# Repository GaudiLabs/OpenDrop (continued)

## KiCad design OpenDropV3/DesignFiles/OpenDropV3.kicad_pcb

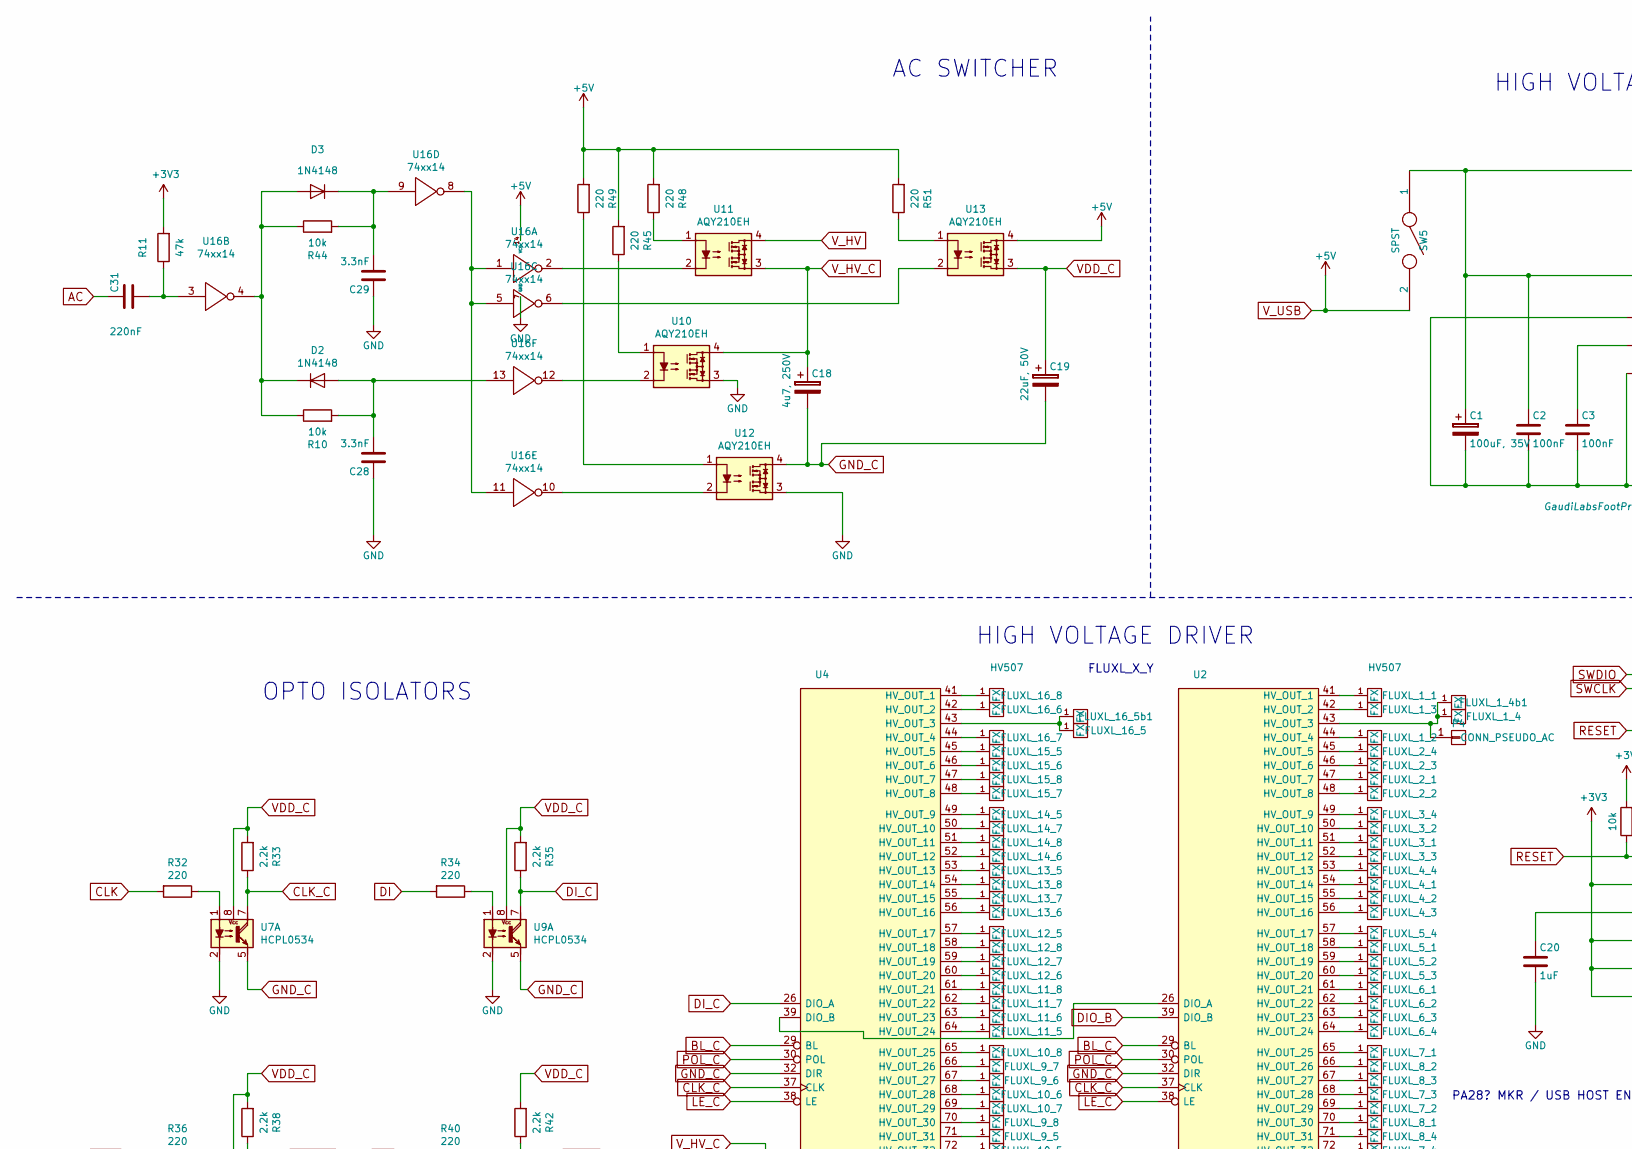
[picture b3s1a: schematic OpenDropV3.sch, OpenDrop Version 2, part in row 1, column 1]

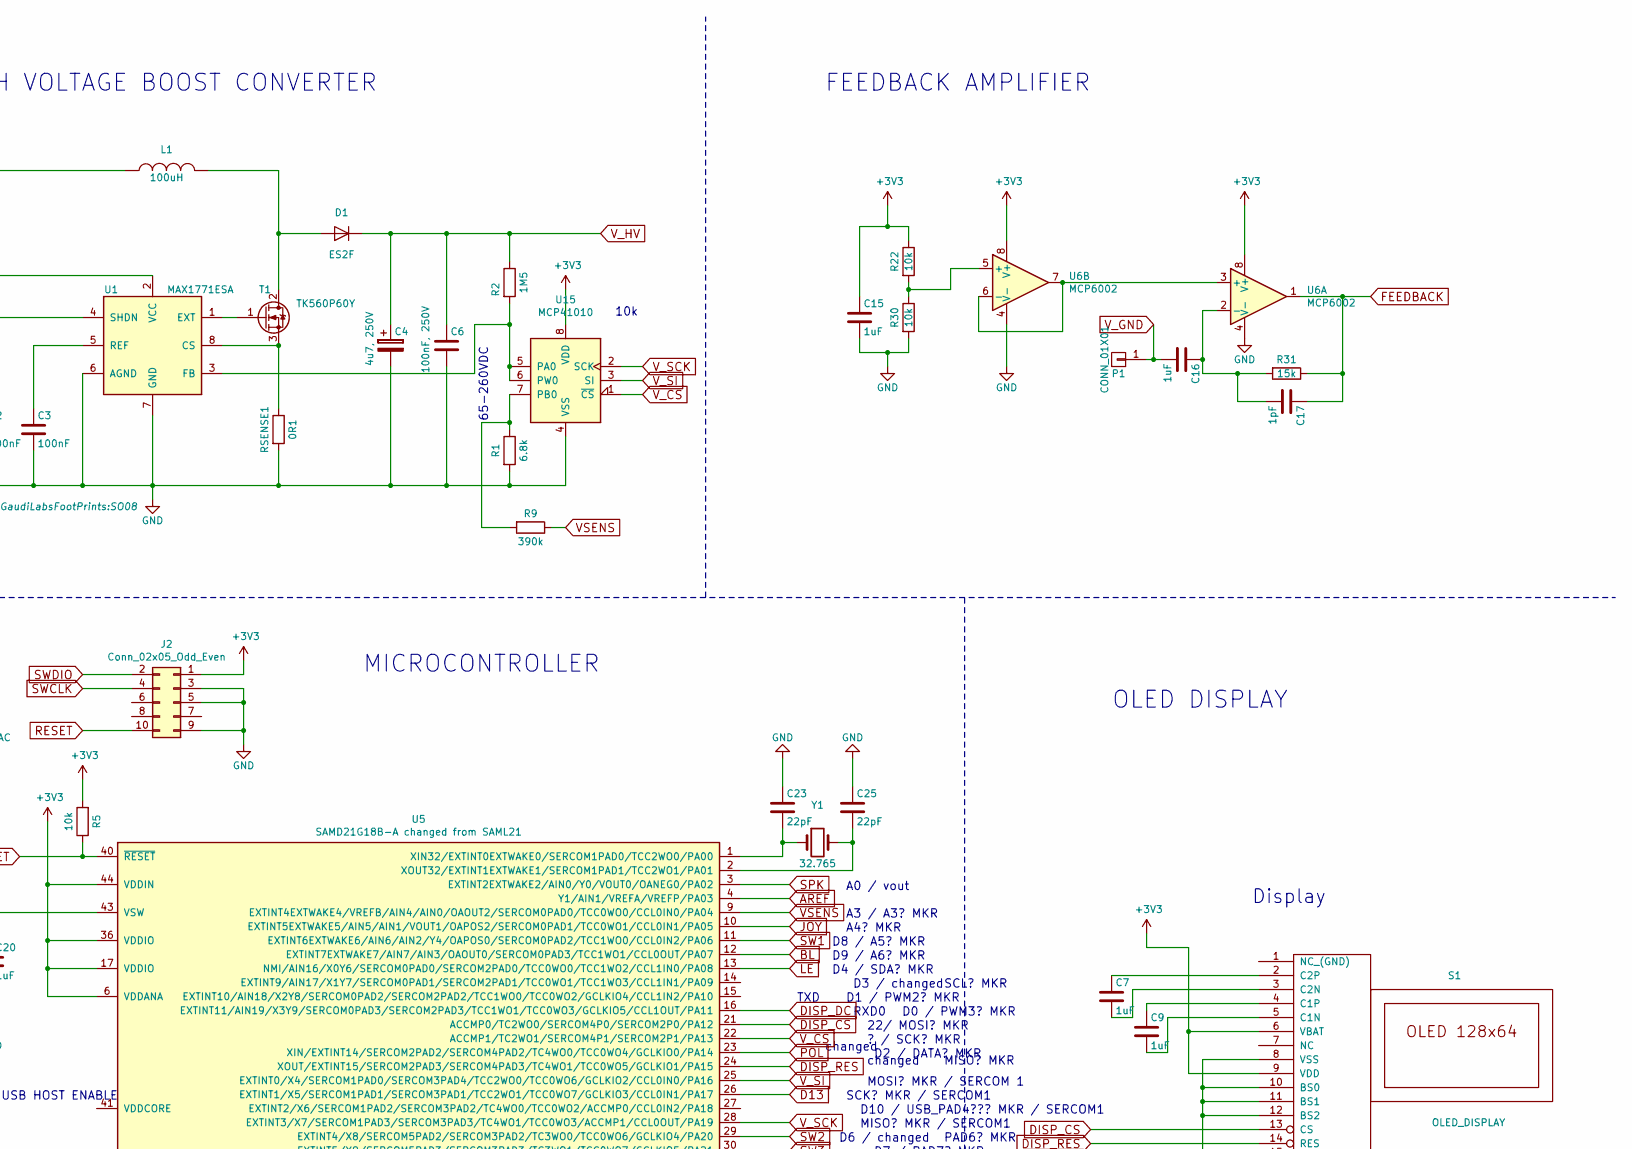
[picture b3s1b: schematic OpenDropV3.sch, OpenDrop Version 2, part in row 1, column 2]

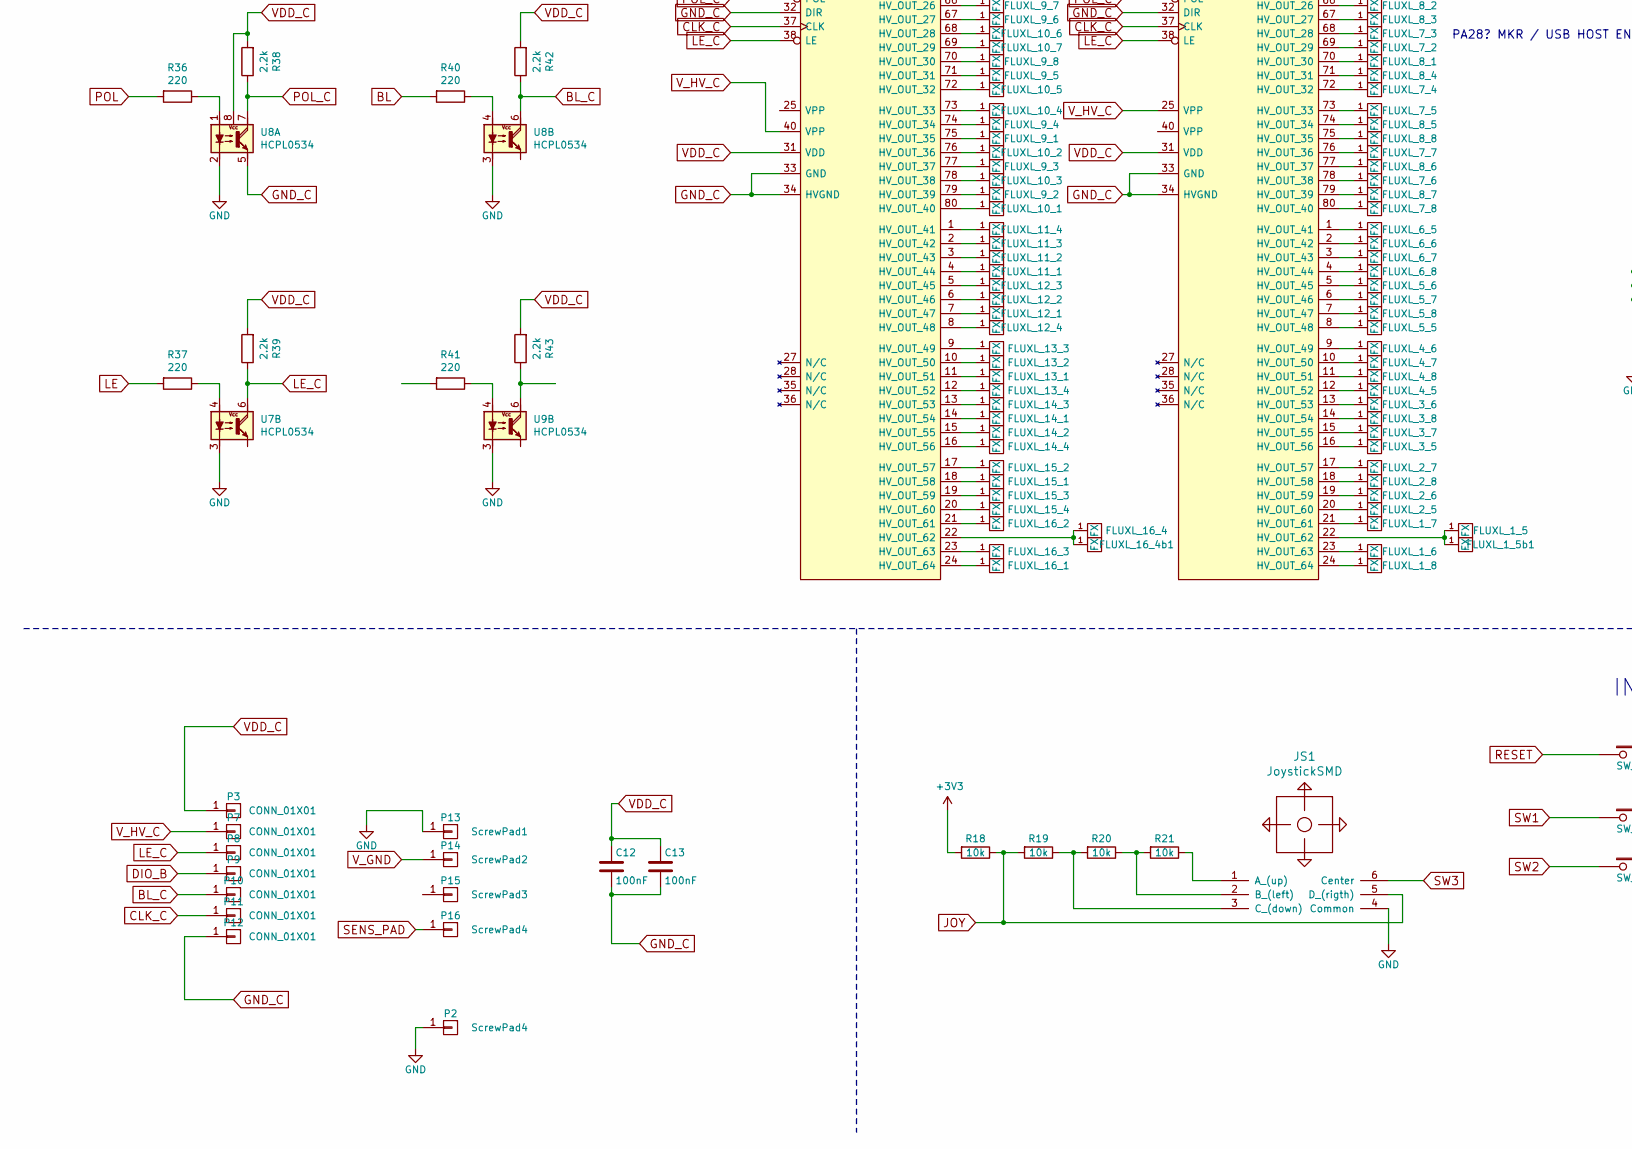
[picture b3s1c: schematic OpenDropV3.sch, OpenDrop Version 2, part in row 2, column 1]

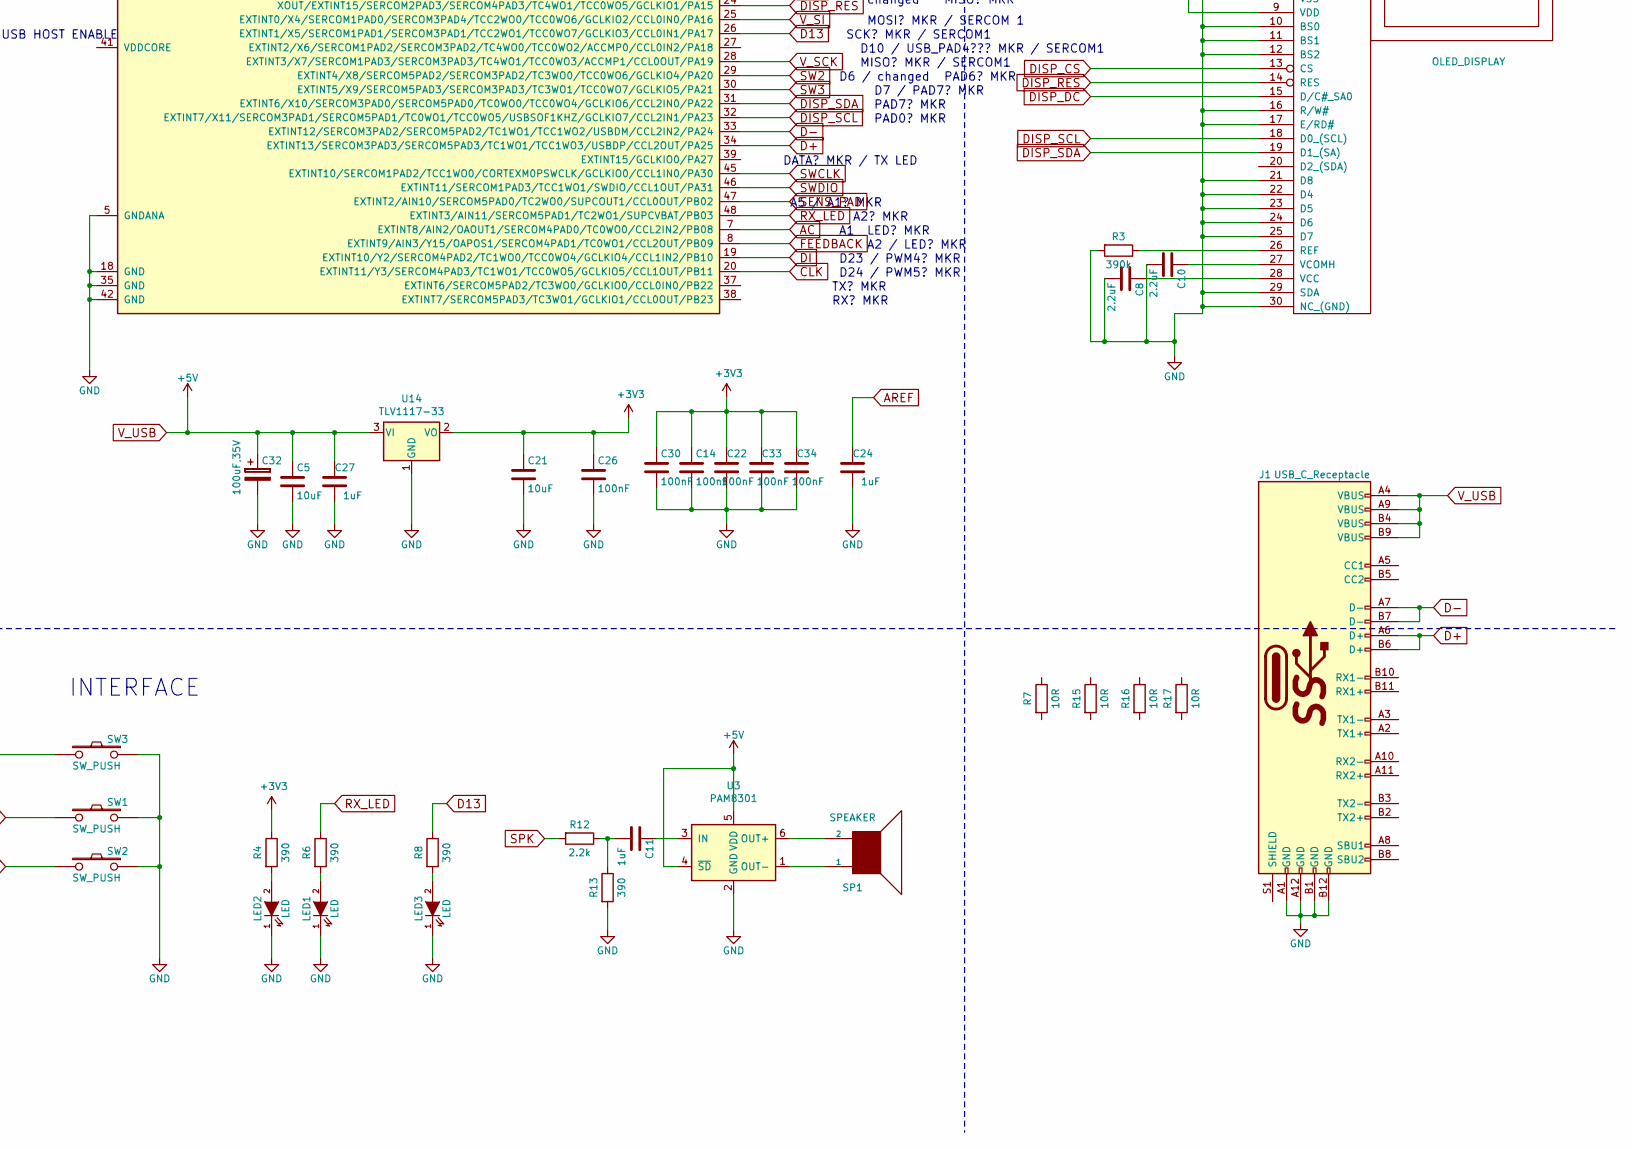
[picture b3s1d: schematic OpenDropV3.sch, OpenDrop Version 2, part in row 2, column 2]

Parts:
C1: 100uF, 35V; R_2512_HandSoldering
C2, C3, C12, C13, C14, C22, C26, C30, C33, C34: 100nF; C_0805
C4, C18: 4u7, 250V; c_elec_10x10
C5, C21: 10uF; C_1206
C6: 100nF, 250V; C_1913
C7, C9, C11, C15, C16, C20, C24, C27: 1uF; C_0805
C8, C10: 2.2uF; C_0805
C17: 1pF; C_0805
C19: 22uF, 50V; c_elec_6.3x5.8
C23, C25: 22pF; C_0805
C28, C29: 3.3nF; C_0805
C31: 220nF; C_0805
C32: 100uF,35V; R_2512_HandSoldering
D1: ES2F; DO-214AA
D2, D3: 1N4148; D_SOD-323
FLUXL_1_1, FLUXL_1_8, FLUXL_16_1, FLUXL_16_8: FX; FLUXPAD_2_75_4MIL_4_5_res3
FLUXL_1_2, FLUXL_1_7, FLUXL_16_2, FLUXL_16_7: FX; FLUXPAD_2_75_4MIL_4_5_res1
FLUXL_1_3, FLUXL_1_6, FLUXL_16_3, FLUXL_16_6: FX; FLUXPAD_2_75_4MIL_4_5_res2
FLUXL_1_4, FLUXL_1_5, FLUXL_16_4, FLUXL_16_5: FX; FLUXPAD_2_75_4MIL_4_5_res4
FLUXL_1_4b1, FLUXL_1_5b1, FLUXL_16_4b1, FLUXL_16_5b1: FX; FLUXPAD_2_75_4MIL_4_5_res5
FLUXL_2_1, FLUXL_15_8: FX; FLUXPAD_2_75_4MIL_4_5_topleft
FLUXL_2_2, FLUXL_2_7, FLUXL_3_2, FLUXL_3_3, FLUXL_3_4, FLUXL_3_5, FLUXL_3_6, FLUXL_3_7, FLUXL_4_2, FLUXL_4_3, FLUXL_4_4, FLUXL_4_5, FLUXL_4_6, FLUXL_4_7, FLUXL_5_2, FLUXL_5_3, FLUXL_5_4, FLUXL_5_5, FLUXL_5_6, FLUXL_5_7, FLUXL_6_2, FLUXL_6_3, FLUXL_6_4, FLUXL_6_5, FLUXL_6_6, FLUXL_6_7, FLUXL_7_2, FLUXL_7_3, FLUXL_7_4, FLUXL_7_5, FLUXL_7_6, FLUXL_7_7, FLUXL_8_2, FLUXL_8_3, FLUXL_8_4, FLUXL_8_5, FLUXL_8_6, FLUXL_8_7, FLUXL_9_2, FLUXL_9_3, FLUXL_9_4, FLUXL_9_5, FLUXL_9_6, FLUXL_9_7, FLUXL_10_2, FLUXL_10_3, FLUXL_10_4, FLUXL_10_5, FLUXL_10_6, FLUXL_10_7, FLUXL_11_2, FLUXL_11_3, FLUXL_11_4, FLUXL_11_5, FLUXL_11_6, FLUXL_11_7, FLUXL_12_2, FLUXL_12_3, FLUXL_12_4, FLUXL_12_5, FLUXL_12_6, FLUXL_12_7, FLUXL_13_2, FLUXL_13_3, FLUXL_13_4, FLUXL_13_5, FLUXL_13_6, FLUXL_13_7, FLUXL_14_2, FLUXL_14_3, FLUXL_14_4, FLUXL_14_5, FLUXL_14_6, FLUXL_14_7, FLUXL_15_2, FLUXL_15_7: FX; FLUXPAD_2_75_4MIL_4_5
FLUXL_2_3, FLUXL_2_4, FLUXL_2_5, FLUXL_2_6, FLUXL_15_3, FLUXL_15_4, FLUXL_15_5, FLUXL_15_6: FX; FLUXPAD_2_75_4MIL_4_5_side
FLUXL_2_8, FLUXL_15_1: FX; FLUXPAD_2_75_4MIL_4_5_topright
FLUXL_3_1, FLUXL_3_8, FLUXL_4_1, FLUXL_4_8, FLUXL_5_1, FLUXL_5_8, FLUXL_6_1, FLUXL_6_8, FLUXL_7_1, FLUXL_7_8, FLUXL_8_1, FLUXL_8_8, FLUXL_9_1, FLUXL_9_8, FLUXL_10_1, FLUXL_10_8, FLUXL_11_1, FLUXL_11_8, FLUXL_12_1, FLUXL_12_8, FLUXL_13_1, FLUXL_13_8, FLUXL_14_1, FLUXL_14_8: FX; FLUXPAD_2_75_4MIL_4_5_top
J1: USB_C_Receptacle; USB_C_Receptacle_Amphenol_12401610E4-2A
J2: Conn_02x05_Odd_Even; Pin_Header_Straight_2x05_Pitch1.27mm_SMD
JS1: JoystickSMD; JoystickSMD_SKQUSeries
L1: 100uH; SRN1060
LED1, LED2, LED3: LED; LED-0805
P1, P3, P7, P8, P9, P10, P11, P12: CONN_01X01; Measurement_Point_Square-SMD-Pad_Small
P2: ScrewPad4; Measurement_Point_Croki
P4: CONN_PSEUDO_AC; Measurement_Point_Square-SMD-Pad_Small
P13: ScrewPad1; MountingHolePad_3x9mm
P14: ScrewPad2; MountingHolePad_3x9mm
P15: ScrewPad3; MountingHolePad_3x9mm
P16: ScrewPad4; MountingHolePad_3x9mm
R1: 6.8k; R_0805
R2: 1M5; R_2512
R3, R9: 390k; R_0805
R4, R6, R8, R13: 390; R_0805
R5, R10, R18, R19, R20, R21, R22, R30, R44: 10k; R_0805
R7, R15, R16, R17: 10R; R_0805_HeatPad
R11: 47k; R_0805
R12, R33, R35, R38, R39, R42, R43: 2.2k; R_0805
R31: 15k; R_0805
R32, R34, R36, R37, R40, R41, R45, R48, R49, R51: 220; R_0805
RSENSE1: 0R1; R_2010
S1: OLED_DISPLAY; OLED_096_1_Flip
SP1: SPEAKER; Speaker16mm
SW1, SW2: SW_PUSH; PUSH_BUTTON_SMD
SW3: SW_PUSH; SW_SPST_KMS221GLFS
SW5: SPST; Switch_On-On
T1: TK560P60Y; D-Pak_TO252AA
U1: MAX1771ESA; SO08
U2, U4: HV507; PQFP-80_14x20mm_Pitch0.8mm
U3: PAM8301; SOT-23-6
U5: SAMD21G18B-A changed from SAML21; TQFP-48_7x7mm_Pitch0.5mm
U6: MCP6002; SO08
U7, U8, U9: HCPL0534; HCPL_Optocoupler_SMD
U10, U11, U12, U13: AQY210EH; SMD_DIP4
U14: TLV1117-33; SOT-223
U15: MCP41010; SO08
U16: 74xx14; SOIC-14_N
Y1: 32.765; Crystal_SMD_3215-2pin_3.2x1.5mm

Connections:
+3V3: C14.1, C15.1, C21.1, C22.2, C26.1, C30.1, C33.2, C34.2, J2.1, R4.1, R5.2, R11.2, R18.2, R22.1, S1.6 (VBAT), S1.9 (VDD), U5.6 (VDDANA), U5.17 (VDDIO), U5.36 (VDDIO), U5.44 (VDDIN), U6.8 (V+), U14.2 (VO), U15.8 (VDD)
AC: C31.1, U5.7 (EXTINT8/AIN2/OAOUT1/SERCOM4PAD0/TC0WO0/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)
AREF: C24.2, U5.4 (Y1/AIN1/VREFA/VREFP/PA03)
BL: R40.2, U5.12 (EXTINT7EXTWAKE7/AIN7/AIN3/OAOUT0/SERCOM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)
BL_C: P10.1, R42.1, U2.29 (BL), U4.29 (BL), U8.6 (COLLECTOR)
CLK: R32.2, U5.20 (EXTINT11/Y3/SERCOM4PAD3/TC1WO1/TCC0WO5/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)
CLK_C: P11.1, R33.1, U2.37 (CLK), U4.37 (CLK), U7.7 (COLLECTOR)
D13: R8.1, U5.26 (EXTINT1/X5/SERCOM1PAD1/SERCOM3PAD1/TCC2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)
D+: J1.A6 (D+), J1.B6 (D+), U5.34 (EXTINT13/SERCOM3PAD3/SERCOM5PAD3/TC1WO1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)
D-: J1.A7 (D-), J1.B7 (D-), U5.33 (EXTINT12/SERCOM3PAD2/SERCOM5PAD2/TC1WO1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)
DI: R34.2, U5.19 (EXTINT10/Y2/SERCOM4PAD2/TC1WO0/TCC0WO4/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)
DIO_B: P9.1, U2.39 (DIO_B)
DISP_CS: S1.13 (CS), U5.21 (ACCMP0/TC2WO0/SERCOM4P0/SERCOM2P0/PA12)
DISP_DC: S1.15 (D/C#_SA0), U5.16 (EXTINT11/AIN19/X3Y9/SERCOM0PAD3/SERCOM2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)
DISP_RES: S1.14 (RES), U5.24 (XOUT/EXTINT15/SERCOM2PAD3/SERCOM4PAD3/T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)
DISP_SCL: S1.18 (D0_(SCL)), U5.32 (EXTINT7/X11/SERCOM3PAD1/SERCOM5PAD1/TC0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)
DISP_SDA: S1.19 (D1_(SA)), U5.31 (EXTINT6/X10/SERCOM3PAD0/SERCOM5PAD0/TC0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)
DI_C: R35.1, U4.26 (DIO_A), U9.7 (COLLECTOR)
FEEDBACK: C17.1, R31.1, U5.8 (EXTINT9/AIN3/Y15/OAPOS1/SERCOM4PAD1/TC0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), U6.1
GND: C1.2, C2.2, C3.2, C4.2, C5.2, C6.2, C8.2, C10.2, C14.2, C15.2, C20.2, C21.2, C22.1, C23.1, C24.1, C25.1, C26.2, C27.1, C28.1, C29.1, C30.2, C32.2, C33.1, C34.1, J1.A1 (GND), J1.A12 (GND), J1.B1 (GND), J1.B12 (GND), J2.3, J2.5, J2.9, JS1.4 (Common), LED1.1 (K), LED2.1 (K), LED3.1 (K), P2.1, P13.1, R1.2, R3.2, R13.2, R30.2, RSENSE1.2, S1.8 (VSS), S1.10 (BS0), S1.11 (BS1), S1.12 (BS2), S1.16 (R/W#), S1.17 (E/RD#), S1.21 (D8), S1.22 (D4), S1.23 (D5), S1.24 (D6), S1.25 (D7), S1.29 (SDA), S1.30 (NC_(GND)), SW1.2, SW2.2, SW3.2, U1.4 (SHDN), U1.6 (AGND), U1.7 (GND), U3.2 (GND), U5.5 (GNDANA), U5.18 (GND), U5.35 (GND), U5.42 (GND), U6.4 (V-), U7.2 (CATHODE), U7.3 (CATHODE), U8.2 (CATHODE), U8.3 (CATHODE), U9.2 (CATHODE), U9.3 (CATHODE), U10.3, U12.3, U14.1 (GND), U15.4 (VSS), U16.7 (GND)
GND_C: C12.2, C13.2, C18.2, C19.2, P12.1, U2.32 (DIR), U2.33 (GND), U2.34 (HVGND), U4.32 (DIR), U4.33 (GND), U4.34 (HVGND), U7.5, U8.5, U9.5, U12.4
JOY: JS1.5 (D_(rigth)), R18.1, R19.2, U5.10 (EXTINT5EXTWAKE5/AIN5/AIN1/VOUT1/OAPOS2/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)
LE: R37.2, U5.13 (NMI/AIN16/X0Y6/SERCOM0PAD0/SERCOM2PAD0/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)
LE_C: P8.1, R39.1, U2.38 (LE), U4.38 (LE), U7.6 (COLLECTOR)
unnamed: C1.1, C2.1, L1.1, SW5.1, U1.2 (VCC)
unnamed: C3.1, U1.5 (REF)
unnamed: C7.1, S1.2 (C2P)
unnamed: C7.2, S1.3 (C2N)
unnamed: C8.1, S1.28 (VCC)
unnamed: C9.1, S1.4 (C1P)
unnamed: C9.2, S1.5 (C1N)
unnamed: C10.1, S1.27 (VCOMH)
unnamed: C11.1, R12.1, R13.1
unnamed: C11.2, U3.3 (IN)
unnamed: C16.1, C17.2, R31.2, U6.2 (-)
unnamed: C20.1, U5.43 (VSW)
unnamed: C23.2, U5.1 (XIN32/EXTINT0EXTWAKE0/SERCOM1PAD0/TCC2W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), Y1.1
unnamed: C25.2, U5.2 (XOUT32/EXTINT1EXTWAKE1/SERCOM1PAD1/TCC2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), Y1.2
unnamed: C28.2, D2.2 (A), R10.2, U16.13
unnamed: C29.2, D3.1 (K), R44.2, U16.9
unnamed: C31.2, R11.1, U16.3
unnamed: D1.2 (A), L1.2, T1.2 (D)
unnamed: D2.1 (K), D3.2 (A), R10.1, R44.1, U16.4
unnamed: FLUXL_1_1.1, U2.41 (HV_OUT_1)
unnamed: FLUXL_1_2.1, U2.44 (HV_OUT_4)
unnamed: FLUXL_1_3.1, U2.42 (HV_OUT_2)
unnamed: FLUXL_1_4.1, FLUXL_1_4b1.1, P4.1, U2.43 (HV_OUT_3)
unnamed: FLUXL_1_5.1, FLUXL_1_5b1.1, U2.22 (HV_OUT_62)
unnamed: FLUXL_1_6.1, U2.23 (HV_OUT_63)
unnamed: FLUXL_1_7.1, U2.21 (HV_OUT_61)
unnamed: FLUXL_1_8.1, U2.24 (HV_OUT_64)
unnamed: FLUXL_2_1.1, U2.47 (HV_OUT_7)
unnamed: FLUXL_2_2.1, U2.48 (HV_OUT_8)
unnamed: FLUXL_2_3.1, U2.46 (HV_OUT_6)
unnamed: FLUXL_2_4.1, U2.45 (HV_OUT_5)
unnamed: FLUXL_2_5.1, U2.20 (HV_OUT_60)
unnamed: FLUXL_2_6.1, U2.19 (HV_OUT_59)
unnamed: FLUXL_2_7.1, U2.17 (HV_OUT_57)
unnamed: FLUXL_2_8.1, U2.18 (HV_OUT_58)
unnamed: FLUXL_3_1.1, U2.51 (HV_OUT_11)
unnamed: FLUXL_3_2.1, U2.50 (HV_OUT_10)
unnamed: FLUXL_3_3.1, U2.52 (HV_OUT_12)
unnamed: FLUXL_3_4.1, U2.49 (HV_OUT_9)
unnamed: FLUXL_3_5.1, U2.16 (HV_OUT_56)
unnamed: FLUXL_3_6.1, U2.13 (HV_OUT_53)
unnamed: FLUXL_3_7.1, U2.15 (HV_OUT_55)
unnamed: FLUXL_3_8.1, U2.14 (HV_OUT_54)
unnamed: FLUXL_4_1.1, U2.54 (HV_OUT_14)
unnamed: FLUXL_4_2.1, U2.55 (HV_OUT_15)
unnamed: FLUXL_4_3.1, U2.56 (HV_OUT_16)
unnamed: FLUXL_4_4.1, U2.53 (HV_OUT_13)
unnamed: FLUXL_4_5.1, U2.12 (HV_OUT_52)
unnamed: FLUXL_4_6.1, U2.9 (HV_OUT_49)
unnamed: FLUXL_4_7.1, U2.10 (HV_OUT_50)
unnamed: FLUXL_4_8.1, U2.11 (HV_OUT_51)
unnamed: FLUXL_5_1.1, U2.58 (HV_OUT_18)
unnamed: FLUXL_5_2.1, U2.59 (HV_OUT_19)
unnamed: FLUXL_5_3.1, U2.60 (HV_OUT_20)
unnamed: FLUXL_5_4.1, U2.57 (HV_OUT_17)
unnamed: FLUXL_5_5.1, U2.8 (HV_OUT_48)
unnamed: FLUXL_5_6.1, U2.5 (HV_OUT_45)
unnamed: FLUXL_5_7.1, U2.6 (HV_OUT_46)
unnamed: FLUXL_5_8.1, U2.7 (HV_OUT_47)
unnamed: FLUXL_6_1.1, U2.61 (HV_OUT_21)
unnamed: FLUXL_6_2.1, U2.62 (HV_OUT_22)
unnamed: FLUXL_6_3.1, U2.63 (HV_OUT_23)
unnamed: FLUXL_6_4.1, U2.64 (HV_OUT_24)
unnamed: FLUXL_6_5.1, U2.1 (HV_OUT_41)
unnamed: FLUXL_6_6.1, U2.2 (HV_OUT_42)
unnamed: FLUXL_6_7.1, U2.3 (HV_OUT_43)
unnamed: FLUXL_6_8.1, U2.4 (HV_OUT_44)
unnamed: FLUXL_7_1.1, U2.65 (HV_OUT_25)
unnamed: FLUXL_7_2.1, U2.69 (HV_OUT_29)
unnamed: FLUXL_7_3.1, U2.68 (HV_OUT_28)
unnamed: FLUXL_7_4.1, U2.72 (HV_OUT_32)
unnamed: FLUXL_7_5.1, U2.73 (HV_OUT_33)
unnamed: FLUXL_7_6.1, U2.78 (HV_OUT_38)
unnamed: FLUXL_7_7.1, U2.76 (HV_OUT_36)
unnamed: FLUXL_7_8.1, U2.80 (HV_OUT_40)
unnamed: FLUXL_8_1.1, U2.70 (HV_OUT_30)
unnamed: FLUXL_8_2.1, U2.66 (HV_OUT_26)
unnamed: FLUXL_8_3.1, U2.67 (HV_OUT_27)
unnamed: FLUXL_8_4.1, U2.71 (HV_OUT_31)
unnamed: FLUXL_8_5.1, U2.74 (HV_OUT_34)
unnamed: FLUXL_8_6.1, U2.77 (HV_OUT_37)
unnamed: FLUXL_8_7.1, U2.79 (HV_OUT_39)
unnamed: FLUXL_8_8.1, U2.75 (HV_OUT_35)
unnamed: FLUXL_9_1.1, U4.75 (HV_OUT_35)
unnamed: FLUXL_9_2.1, U4.79 (HV_OUT_39)
unnamed: FLUXL_9_3.1, U4.77 (HV_OUT_37)
unnamed: FLUXL_9_4.1, U4.74 (HV_OUT_34)
unnamed: FLUXL_9_5.1, U4.71 (HV_OUT_31)
unnamed: FLUXL_9_6.1, U4.67 (HV_OUT_27)
unnamed: FLUXL_9_7.1, U4.66 (HV_OUT_26)
unnamed: FLUXL_9_8.1, U4.70 (HV_OUT_30)
unnamed: FLUXL_10_1.1, U4.80 (HV_OUT_40)
unnamed: FLUXL_10_2.1, U4.76 (HV_OUT_36)
unnamed: FLUXL_10_3.1, U4.78 (HV_OUT_38)
unnamed: FLUXL_10_4.1, U4.73 (HV_OUT_33)
unnamed: FLUXL_10_5.1, U4.72 (HV_OUT_32)
unnamed: FLUXL_10_6.1, U4.68 (HV_OUT_28)
unnamed: FLUXL_10_7.1, U4.69 (HV_OUT_29)
unnamed: FLUXL_10_8.1, U4.65 (HV_OUT_25)
unnamed: FLUXL_11_1.1, U4.4 (HV_OUT_44)
unnamed: FLUXL_11_2.1, U4.3 (HV_OUT_43)
unnamed: FLUXL_11_3.1, U4.2 (HV_OUT_42)
unnamed: FLUXL_11_4.1, U4.1 (HV_OUT_41)
unnamed: FLUXL_11_5.1, U4.64 (HV_OUT_24)
unnamed: FLUXL_11_6.1, U4.63 (HV_OUT_23)
unnamed: FLUXL_11_7.1, U4.62 (HV_OUT_22)
unnamed: FLUXL_11_8.1, U4.61 (HV_OUT_21)
unnamed: FLUXL_12_1.1, U4.7 (HV_OUT_47)
unnamed: FLUXL_12_2.1, U4.6 (HV_OUT_46)
unnamed: FLUXL_12_3.1, U4.5 (HV_OUT_45)
unnamed: FLUXL_12_4.1, U4.8 (HV_OUT_48)
unnamed: FLUXL_12_5.1, U4.57 (HV_OUT_17)
unnamed: FLUXL_12_6.1, U4.60 (HV_OUT_20)
unnamed: FLUXL_12_7.1, U4.59 (HV_OUT_19)
unnamed: FLUXL_12_8.1, U4.58 (HV_OUT_18)
unnamed: FLUXL_13_1.1, U4.11 (HV_OUT_51)
unnamed: FLUXL_13_2.1, U4.10 (HV_OUT_50)
unnamed: FLUXL_13_3.1, U4.9 (HV_OUT_49)
unnamed: FLUXL_13_4.1, U4.12 (HV_OUT_52)
unnamed: FLUXL_13_5.1, U4.53 (HV_OUT_13)
unnamed: FLUXL_13_6.1, U4.56 (HV_OUT_16)
unnamed: FLUXL_13_7.1, U4.55 (HV_OUT_15)
unnamed: FLUXL_13_8.1, U4.54 (HV_OUT_14)
unnamed: FLUXL_14_1.1, U4.14 (HV_OUT_54)
unnamed: FLUXL_14_2.1, U4.15 (HV_OUT_55)
unnamed: FLUXL_14_3.1, U4.13 (HV_OUT_53)
unnamed: FLUXL_14_4.1, U4.16 (HV_OUT_56)
unnamed: FLUXL_14_5.1, U4.49 (HV_OUT_9)
unnamed: FLUXL_14_6.1, U4.52 (HV_OUT_12)
unnamed: FLUXL_14_7.1, U4.50 (HV_OUT_10)
unnamed: FLUXL_14_8.1, U4.51 (HV_OUT_11)
unnamed: FLUXL_15_1.1, U4.18 (HV_OUT_58)
unnamed: FLUXL_15_2.1, U4.17 (HV_OUT_57)
unnamed: FLUXL_15_3.1, U4.19 (HV_OUT_59)
unnamed: FLUXL_15_4.1, U4.20 (HV_OUT_60)
unnamed: FLUXL_15_5.1, U4.45 (HV_OUT_5)
unnamed: FLUXL_15_6.1, U4.46 (HV_OUT_6)
unnamed: FLUXL_15_7.1, U4.48 (HV_OUT_8)
unnamed: FLUXL_15_8.1, U4.47 (HV_OUT_7)
unnamed: FLUXL_16_1.1, U4.24 (HV_OUT_64)
unnamed: FLUXL_16_2.1, U4.21 (HV_OUT_61)
unnamed: FLUXL_16_3.1, U4.23 (HV_OUT_63)
unnamed: FLUXL_16_4.1, FLUXL_16_4b1.1, U4.22 (HV_OUT_62)
unnamed: FLUXL_16_5.1, FLUXL_16_5b1.1, U4.43 (HV_OUT_3)
unnamed: FLUXL_16_6.1, U4.42 (HV_OUT_2)
unnamed: FLUXL_16_7.1, U4.44 (HV_OUT_4)
unnamed: FLUXL_16_8.1, U4.41 (HV_OUT_1)
unnamed: JS1.1 (A_(up)), R21.1
unnamed: JS1.2 (B_(left)), R20.1, R21.2
unnamed: JS1.3 (C_(down)), R19.1, R20.2
unnamed: LED1.2 (A), R6.2
unnamed: LED2.2 (A), R4.2
unnamed: LED3.2 (A), R8.2
unnamed: R1.1, R9.2, U15.7 (PB0)
unnamed: R2.2, U1.3 (FB), U15.5 (PA0), U15.6 (PW0)
unnamed: R3.1, S1.26 (REF)
unnamed: R22.2, R30.1, U6.5 (+)
unnamed: R32.1, U7.1 (ANODE)
unnamed: R34.1, U9.1 (ANODE)
unnamed: R36.1, U8.1 (ANODE)
unnamed: R37.1, U7.4 (ANODE)
unnamed: R40.1, U8.4 (ANODE)
unnamed: R41.1, U9.4 (ANODE)
unnamed: R43.1, U9.6 (COLLECTOR)
unnamed: R45.1, U10.1
unnamed: R48.1, U11.1
unnamed: R49.1, U12.1
unnamed: R51.1, U13.1
unnamed: RSENSE1.1, T1.3 (S), U1.8 (CS)
unnamed: SP1.1, U3.1 (OUT-)
unnamed: SP1.2, U3.6 (OUT+)
unnamed: T1.1 (G), U1.1 (EXT)
unnamed: U2.26 (DIO_A), U4.39 (DIO_B)
unnamed: U6.3 (+), U6.6 (-), U6.7
unnamed: U10.2, U16.12
unnamed: U11.2, U16.2
unnamed: U12.2, U16.10
unnamed: U13.2, U16.6
unnamed: U16.1, U16.5, U16.8, U16.11
POL: R36.2, U5.23 (XIN/EXTINT14/SERCOM2PAD2/SERCOM4PAD2/TC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)
POL_C: R38.1, U2.30 (POL), U4.30 (POL), U8.7 (COLLECTOR)
RESET: J2.10, R5.1, SW3.1, U5.40 (~RESET~)
RX_LED: R6.1, U5.48 (EXTINT3/AIN11/SERCOM5PAD1/TC2WO1/SUPCVB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)
SENS_PAD: P16.1, U5.47 (EXTINT2/AIN10/SERCOM5PAD0/TC2WO0/SUPCOU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)
SPK: R12.2, U5.3 (EXTINT2EXTWAKE2/AIN0/Y0/VOUT0/OANEG0/PA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)
SW1: SW1.1, U5.11 (EXTINT6EXTWAKE6/AIN6/AIN2/Y4/OAPOS0/SER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)
SW2: SW2.1, U5.29 (EXTINT4/X8/SERCOM5PAD2/SERCOM3PAD2/TC3W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)
SW3: JS1.6 (Center), U5.30 (EXTINT5/X9/SERCOM5PAD3/SERCOM3PAD3/TC3W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)
SWCLK: J2.4, U5.45 (EXTINT10/SERCOM1PAD2/TCC1WO0/CORTEXM0PS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)
SWDIO: J2.2, U5.46 (EXTINT11/SERCOM1PAD3/TCC1WO1/SWDIO/CCL1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)
VDD_C: C12.1, C13.1, C19.1, P3.1, R33.2, R35.2, R38.2, R39.2, R42.2, R43.2, U2.31 (VDD), U4.31 (VDD), U7.8 (VCC), U8.8 (VCC), U9.8 (VCC), U13.3
VSENS: R9.1, U5.9 (EXTINT4EXTWAKE4/VREFB/AIN4/AIN0/OAOUT2/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)
V_CS: U5.22 (ACCMP1/TC2WO1/SERCOM4P1/SERCOM2P1/PA13), U15.1 (~CS)
V_GND: C16.2, P1.1, P14.1
V_HV: C4.1, C6.1, D1.1 (K), R2.1, U11.4
V_HV_C: C18.1, P7.1, U2.25 (VPP), U4.40 (VPP), U10.4, U11.3
V_SCK: U5.28 (EXTINT3/X7/SERCOM1PAD3/SERCOM3PAD3/TC4W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), U15.2 (SCK)
V_SI: U5.25 (EXTINT0/X4/SERCOM1PAD0/SERCOM3PAD4/TCC2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), U15.3 (SI)
V_USB: C5.1, C27.2, C32.1, J1.A4 (VBUS), J1.A9 (VBUS), J1.B4 (VBUS), J1.B9 (VBUS), R45.2, R48.2, R49.2, R51.2, SW5.2, U3.4 (~SD), U3.5 (VDD), U13.4, U14.3 (VI), U16.14 (VCC)

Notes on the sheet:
65-260VDC
Display
AC SWITCHER
HIGH VOLTAGE BOOST CONVERTER
FEEDBACK AMPLIFIER
INTERFACE
HIGH VOLTAGE DRIVER
OPTO ISOLATORS
MICROCONTROLLER
OLED DISPLAY
D6 / changed
A0 / vout
changed
10k
D3 / changed
LED? MKR
A3 / A3? MKR
A4? MKR
D8 / A5? MKR
D9 / A6? MKR
D4 / SDA? MKR
SCL? MKR
D1 / PWM2? MKR
D0 / PWM3? MKR
D23 / PWM4? MKR
D24 / PWM5? MKR
22/ MOSI? MKR
? / SCK? MKR
D2 / DATA? MKR
MISO? MKR
MOSI? MKR / SERCOM 1
SCK? MKR / SERCOM1
D10 / USB_PAD4??? MKR / SERCOM1
MISO? MKR / SERCOM1
PAD6? MKR
D7 / PAD7? MKR
PAD7? MKR
PAD0? MKR
TX? MKR
RX? MKR

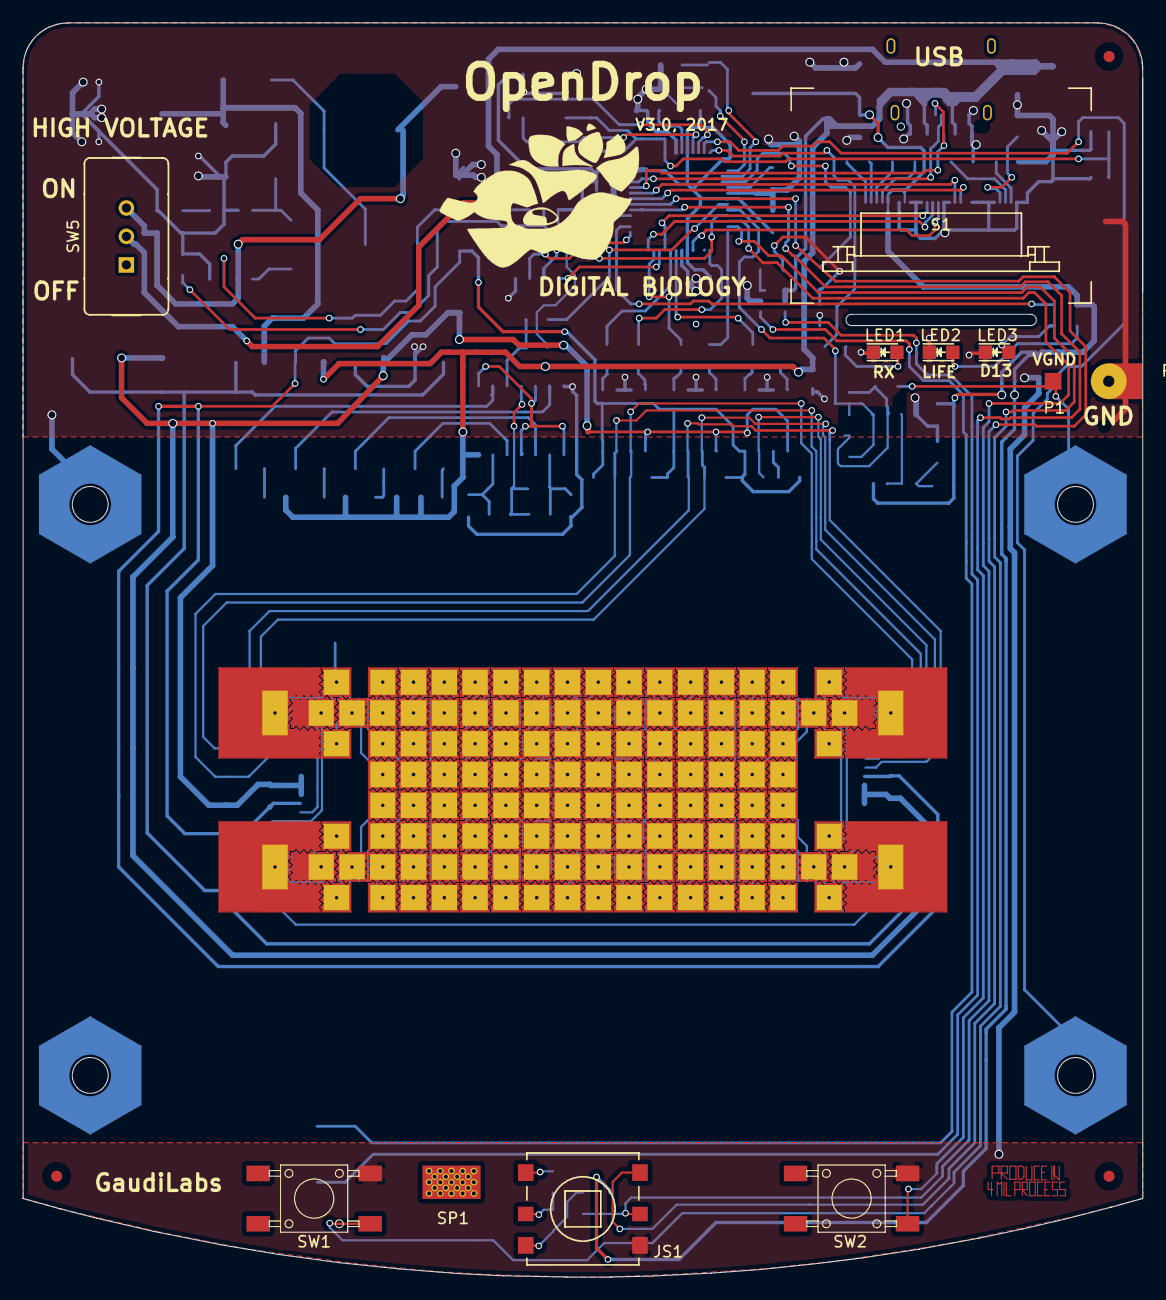
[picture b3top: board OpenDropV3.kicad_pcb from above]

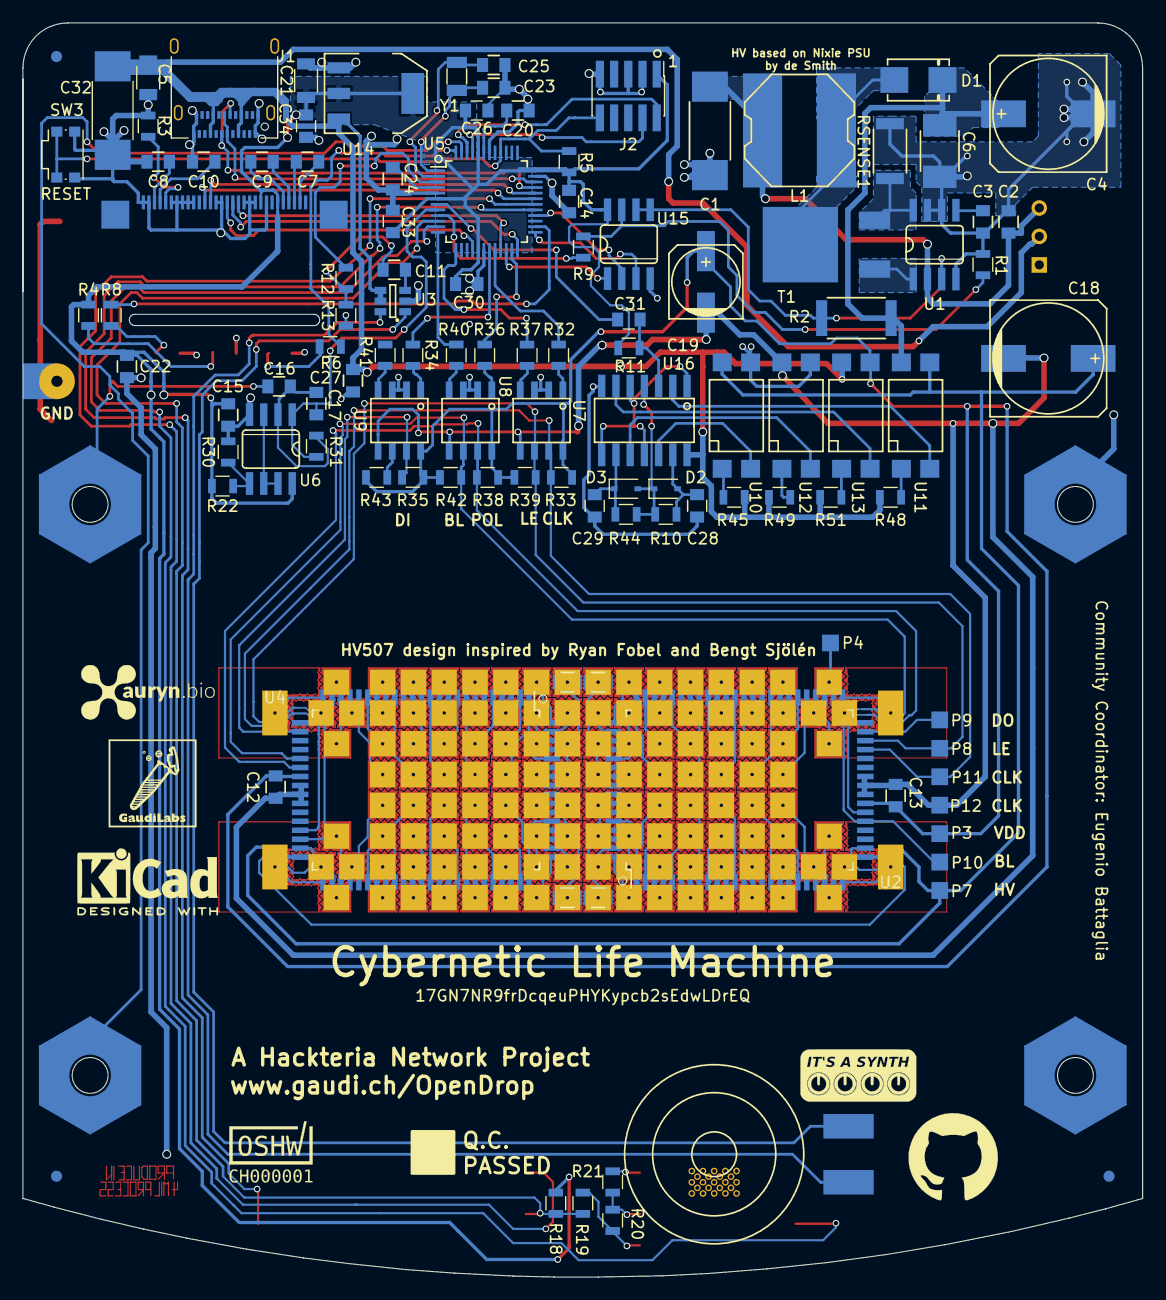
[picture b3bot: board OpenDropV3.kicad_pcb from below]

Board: 2 copper layers, 100.0 x 112.0 mm, 255 parts (108 on the bottom side), 223 nets.
